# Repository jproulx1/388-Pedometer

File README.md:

# 388-Pedometer
Github repository for 388 design project

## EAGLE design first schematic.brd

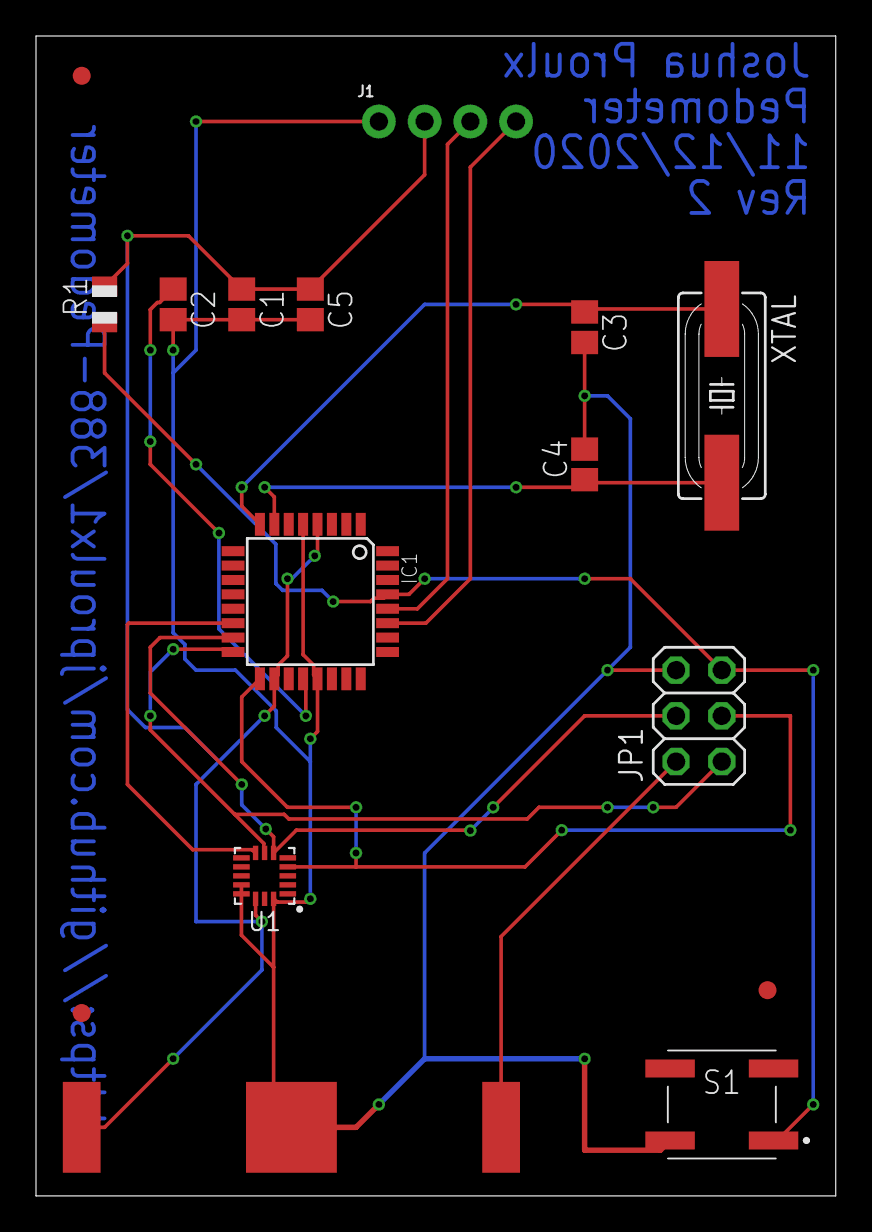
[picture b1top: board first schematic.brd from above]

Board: 2 copper layers, 44.4 x 64.4 mm, 16 parts (0 on the bottom side), 12 nets.

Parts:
C1, C2: 100nF; C0805
C3, C4: 20pF; C0805
C5: 1uF; C0805
IC1: ATMEGA328P; TQFP32-08
J1: 1X04_NO_SILK
JP1: PINHD-2X3; 2X03
R1: 10K; R0805
S1: EVP-BFAC1A000; EVPBFAC1A000
U1: ADXL362; TFLGA-16/3.3MMX3.1MM
U$1, U$2, U$3: FIDUCIAL; FIDUCIAL_1MM
U$4: CR2032
XTAL: 16MHz; HC49UP

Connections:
AREFTOCAP: C2.1, IC1.20
GRND: C1.2, C2.2, C3.2, C4.2, C5.2, IC1.5, IC1.21, J1.1, JP1.6, S1.A2, U1.12, U1.13, U1.16, U$4.GRND
unnamed: C4.1, IC1.7, XTAL.2
unnamed: IC1.15, JP1.4, U1.6
unnamed: IC1.16, JP1.1, U1.7
unnamed: IC1.17, JP1.3, U1.4
unnamed: IC1.29, JP1.5, R1.1, S1.A1
unnamed: C3.1, IC1.8, XTAL.1
unnamed: IC1.28, J1.3
unnamed: IC1.27, J1.4
unnamed: IC1.14, U1.8
VCC: C1.1, C5.1, IC1.4, IC1.18, J1.2, JP1.2, R1.2, U1.14, U$4.VCC, U$4.VCC2

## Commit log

2020-11-06 verification and export
2020-11-12 Rev2
2020-12-01 fixed issues with schematic
2020-12-02 final update

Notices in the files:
parts and their libraries:
SparkFun-Connectors: Licensing: Creative Commons ShareAlike 4.0 International - https://creativecommons.org/licenses/by-sa/4.0
